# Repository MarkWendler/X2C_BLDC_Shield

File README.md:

# X2C_BLDC_Shield
BLDC motor driver expansion board for X2C+ development board

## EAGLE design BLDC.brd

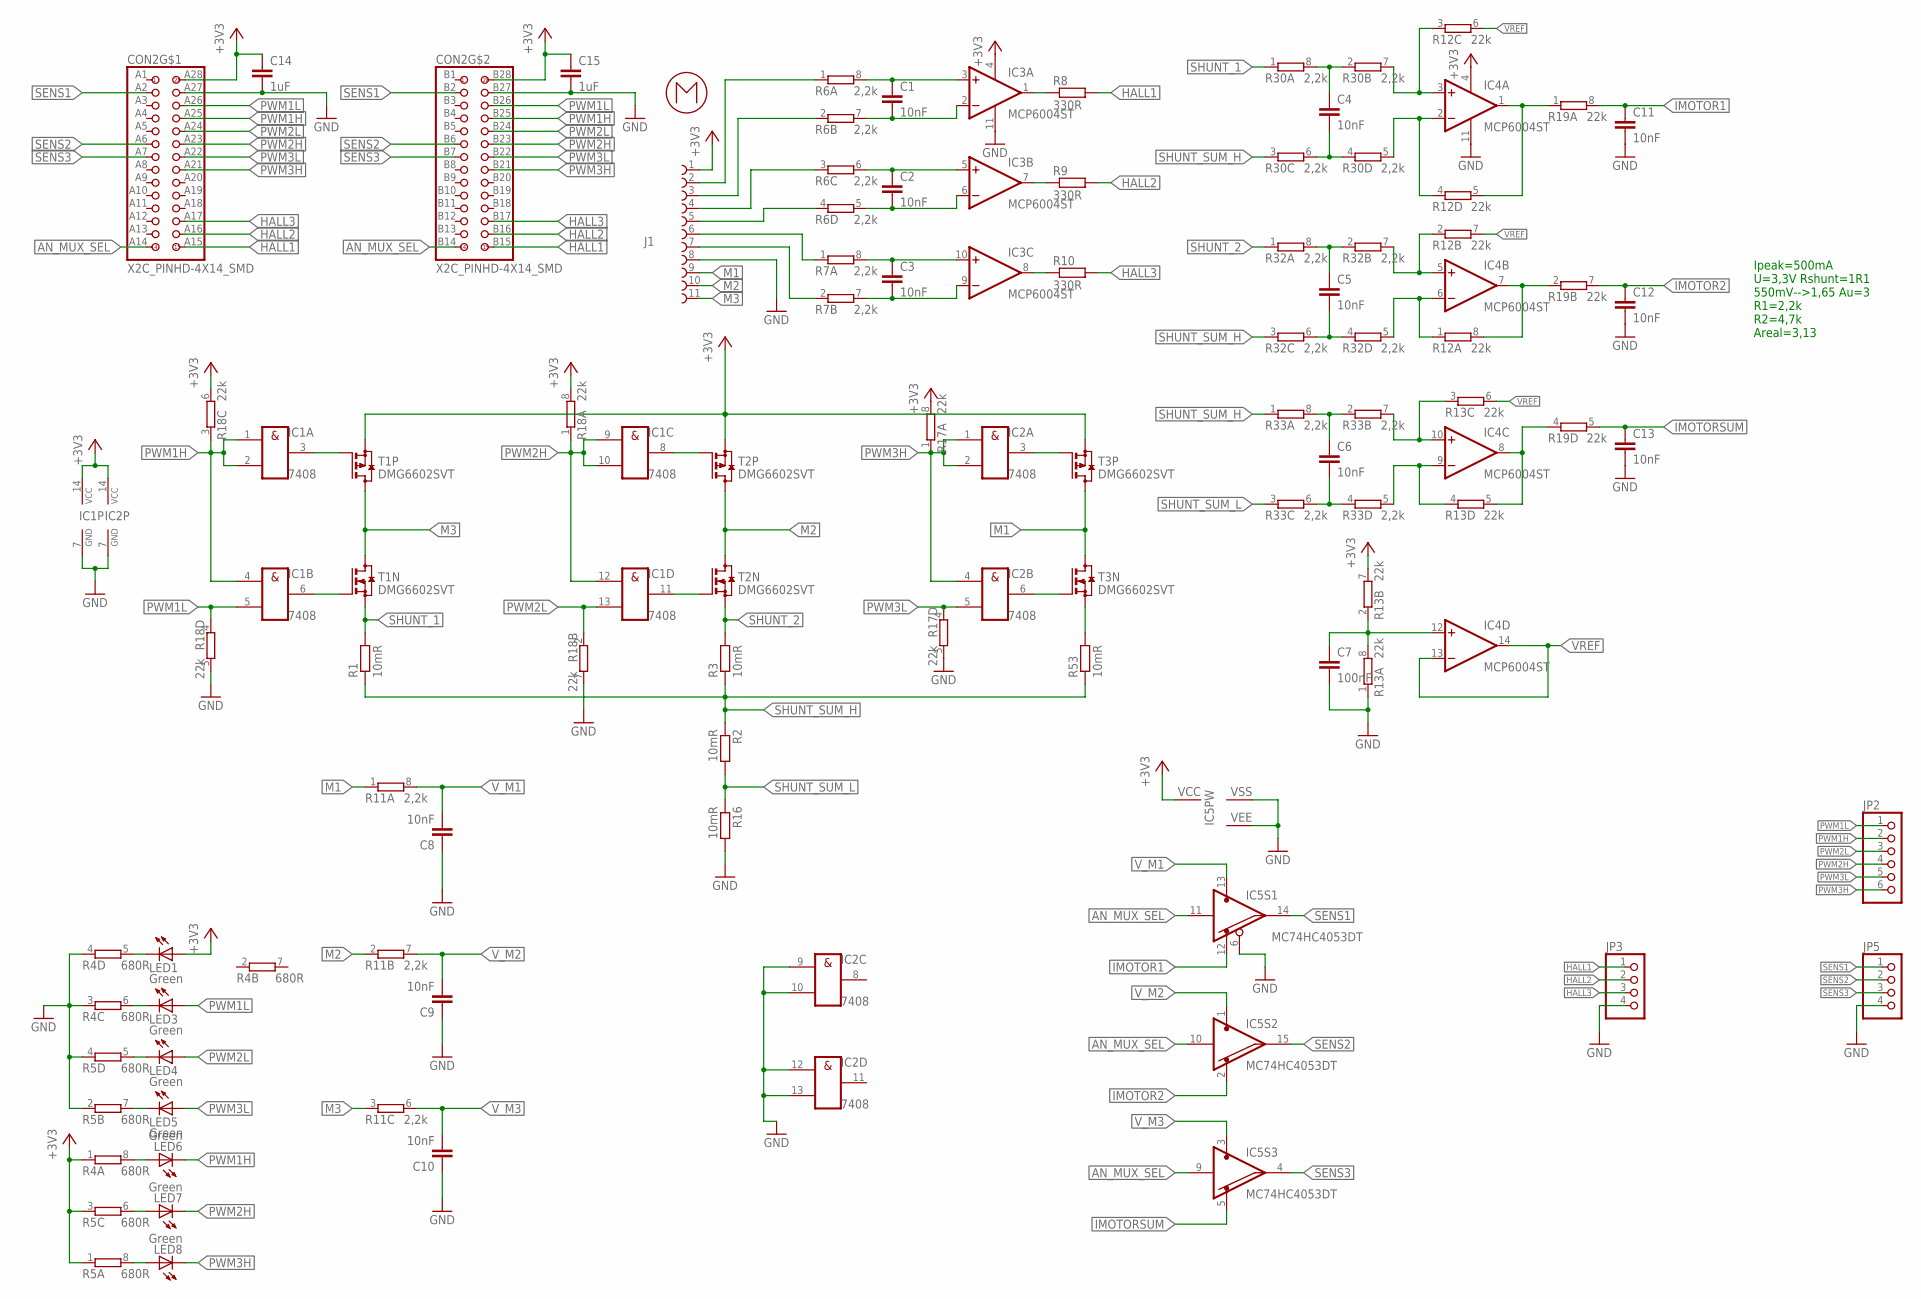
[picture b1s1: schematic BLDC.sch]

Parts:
C1, C2, C3, C4, C5, C6, C8, C9, C10, C11, C12, C13: 10nF; C0603K
C7: 100nF; C0603K
C14, C15: 1uF; C0603K
CON2: X2C_PINHD-4X14_SMD; X2C_4X14_SMD
IC1, IC2: 7408; TSSOP14
IC3, IC4: MCP6004ST; TSSOP14
IC5: MC74HC4053DT; TSSOP16
J1: 68611114122
JP2: PINHD-1X6; 1X06
JP3, JP5: PINHD-1X4; 1X04
LED1, LED3, LED4, LED5, LED6, LED7, LED8: Green; CHIPLED_0805
R1, R2, R3, R16, R53: 10mR; R1206
R4, R5: 680R; EXBV8V_A
R6, R7, R11, R30, R32, R33: 2,2k; EXBV8V_A
R8, R9, R10: 330R; R0603
R12, R13, R17, R18, R19: 22k; EXBV8V_A
T1, T2, T3: DMG6602SVT; TSOT23-6
U$2: BLDC_MOTOR

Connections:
+3V3: C14.1, C15.1, CON2.A28, CON2.B28 (A28), IC1.14 (VCC), IC2.14 (VCC), IC3.4 (V+), IC4.4 (V+), IC5.16 (VCC), J1.1, LED1.A, R4.1, R5.1, R5.3 (1), R13.7 (2), R17.8 (2), R18.6 (2), R18.8 (2), T1.2 (S), T2.2 (S), T3.2 (S)
AN_MUX_SEL: CON2.A14, CON2.B14 (A14), IC5.9 (I), IC5.10 (I), IC5.11 (I)
GND: C7.2, C8.1, C9.1, C10.1, C11.2, C12.2, C13.2, C14.2, C15.2, CON2.A27, CON2.B27 (A27), IC1.7 (GND), IC2.7 (GND), IC2.9 (I0), IC2.10 (I1), IC2.12 (I0), IC2.13 (I1), IC3.11 (V-), IC4.11 (V-), IC5.6, IC5.7 (VEE), IC5.8 (GND), J1.8, JP3.4, JP5.4, R4.3 (1), R4.4 (1), R5.2 (1), R5.4 (1), R13.1, R16.2, R17.5 (2), R18.5 (2), R18.7 (2)
HALL1: CON2.A15, CON2.B15 (A15), JP3.1, R8.2
HALL2: CON2.A16, CON2.B16 (A16), JP3.2, R9.2
HALL3: CON2.A17, CON2.B17 (A17), JP3.3, R10.2
IMOTOR1: C11.1, IC5.12 (O2), R19.8 (2)
IMOTOR2: C12.1, IC5.2 (O2), R19.7 (2)
IMOTORSUM: C13.1, IC5.5 (O2), R19.5 (2)
M1: J1.9, R11.1, T3.4 (D), T3.6 (D)
M2: J1.10, R11.2 (1), T2.4 (D), T2.6 (D)
M3: J1.11, R11.3 (1), T1.4 (D), T1.6 (D)
unnamed: IC1.3 (O), T1.3 (G)
unnamed: IC1.6 (O), T1.1 (G)
unnamed: IC1.8 (O), T2.3 (G)
unnamed: IC1.11 (O), T2.1 (G)
unnamed: IC2.3 (O), T3.3 (G)
unnamed: IC2.6 (O), T3.1 (G)
unnamed: C1.1, IC3.3 (+IN), R6.8 (2)
unnamed: C1.2, IC3.2 (-IN), R6.7 (2)
unnamed: IC4.8 (OUT), R13.5 (2), R19.4 (1)
unnamed: C5.1, R32.2 (1), R32.8 (2)
unnamed: C4.1, R30.2 (1), R30.8 (2)
unnamed: C4.2, R30.4 (1), R30.6 (2)
unnamed: IC4.3 (+IN), R12.3 (1), R30.7 (2)
unnamed: IC4.2 (-IN), R12.4 (1), R30.5 (2)
unnamed: C5.2, R32.4 (1), R32.6 (2)
unnamed: IC4.6 (-IN), R12.1, R32.5 (2)
unnamed: IC4.5 (+IN), R12.2 (1), R32.7 (2)
unnamed: C7.1, IC4.12 (+IN), R13.2 (1), R13.8 (2)
unnamed: IC3.8 (OUT), R10.1
unnamed: LED8.A, R5.8 (2)
unnamed: C6.1, R33.2 (1), R33.8 (2)
unnamed: IC4.10 (+IN), R13.3 (1), R33.7 (2)
unnamed: IC4.9 (-IN), R13.4 (1), R33.5 (2)
unnamed: C6.2, R33.4 (1), R33.6 (2)
unnamed: LED7.A, R5.6 (2)
unnamed: LED5.C, R5.7 (2)
unnamed: IC4.7 (OUT), R12.8 (2), R19.2 (1)
unnamed: C2.1, IC3.5 (+IN), R6.6 (2)
unnamed: LED4.C, R5.5 (2)
unnamed: LED6.A, R4.8 (2)
unnamed: LED3.C, R4.6 (2)
unnamed: LED1.C, R4.5 (2)
unnamed: IC4.1 (OUT), R12.5 (2), R19.1
unnamed: C2.2, IC3.6 (-IN), R6.5 (2)
unnamed: C3.2, IC3.9 (-IN), R7.7 (2)
unnamed: R53.2, T3.5 (S)
unnamed: C3.1, IC3.10 (+IN), R7.8 (2)
unnamed: J1.2, R6.1
unnamed: J1.3, R6.2 (1)
unnamed: J1.4, R6.3 (1)
unnamed: J1.5, R6.4 (1)
unnamed: J1.6, R7.1
unnamed: J1.7, R7.2 (1)
unnamed: IC3.1 (OUT), R8.1
unnamed: IC3.7 (OUT), R9.1
PWM1H: CON2.A25, CON2.B25 (A25), IC1.1 (I0), IC1.2 (I1), IC1.4 (I0), JP2.2, LED6.C, R18.3 (1)
PWM1L: CON2.A26, CON2.B26 (A26), IC1.5 (I1), JP2.1, LED3.A, R18.4 (1)
PWM2H: CON2.A23, CON2.B23 (A23), IC1.9 (I0), IC1.10 (I1), IC1.12 (I0), JP2.4, LED7.C, R18.1
PWM2L: CON2.A24, CON2.B24 (A24), IC1.13 (I1), JP2.3, LED4.A, R18.2 (1)
PWM3H: CON2.A21, CON2.B21 (A21), IC2.1 (I0), IC2.2 (I1), IC2.4 (I0), JP2.6, LED8.C, R17.1
PWM3L: CON2.A22, CON2.B22 (A22), IC2.5 (I1), JP2.5, LED5.A, R17.4 (1)
SENS1: CON2.A2, CON2.B2 (A2), IC5.14 (O), JP5.1
SENS2: CON2.A6, CON2.B6 (A6), IC5.15 (O), JP5.2
SENS3: CON2.A7, CON2.B7 (A7), IC5.4 (O), JP5.3
SHUNT_1: R1.2, R30.1, T1.5 (S)
SHUNT_2: R3.2, R32.1, T2.5 (S)
SHUNT_SUM_H: R1.1, R2.1, R3.1, R30.3 (1), R32.3 (1), R33.1, R53.1
SHUNT_SUM_L: R2.2, R16.1, R33.3 (1)
VREF: IC4.13 (-IN), IC4.14 (OUT), R12.6 (2), R12.7 (2), R13.6 (2)
V_M1: C8.2, IC5.13 (O1), R11.8 (2)
V_M2: C9.2, IC5.1 (O1), R11.7 (2)
V_M3: C10.2, IC5.3 (O1), R11.6 (2)

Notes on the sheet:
Ipeak=500mA U=3,3V Rshunt=1R1 550mV-->1,65 Au=3 R1=2,2k R2=4,7k Areal=3,13

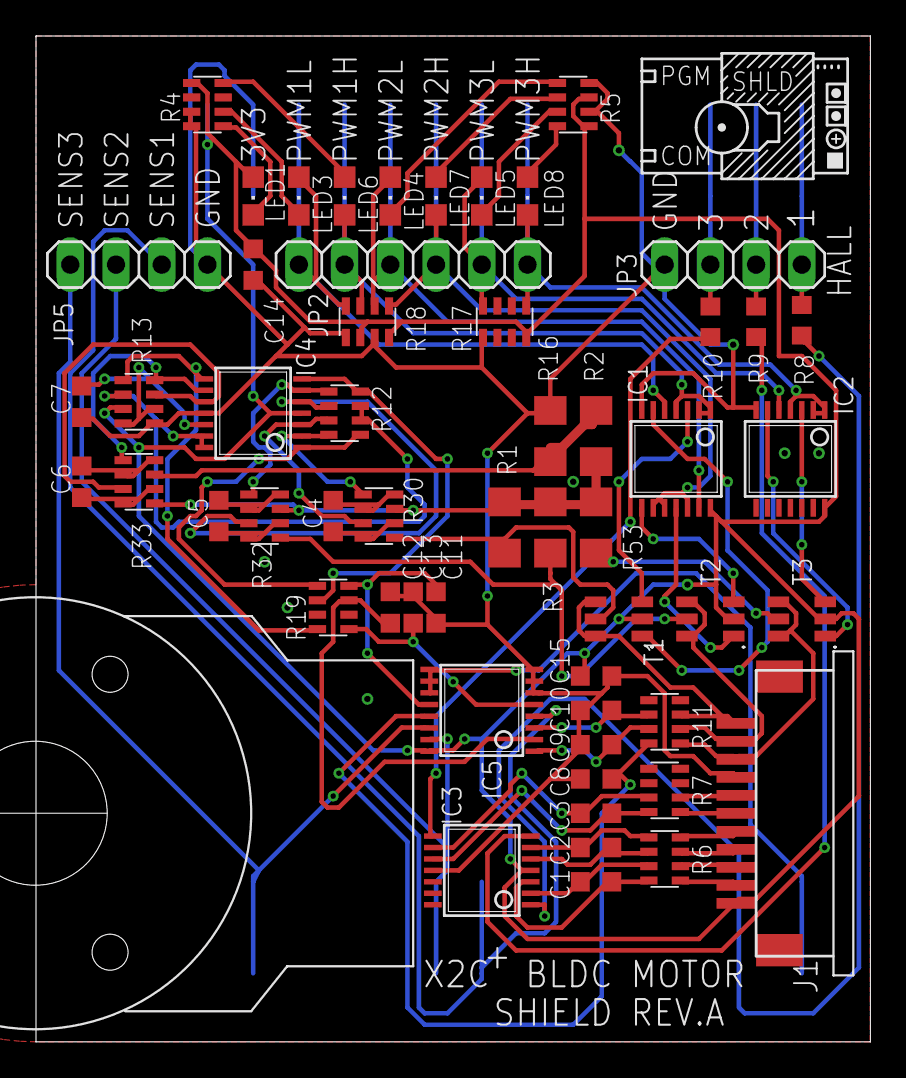
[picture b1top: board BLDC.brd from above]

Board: 2 copper layers, 46.4 x 55.9 mm, 57 parts (1 on the bottom side), 74 nets.

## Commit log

2018-08-02 BLDC REVA
2018-08-02 Added MPLAB X ignore list
    Now the MPLAB X project can be pushed to github
2018-08-02 BLDC spinning project dsPIC
    Full speed BLDC spinning
2020-02-19 Project updated to MPLAB X 5.30 + updated gitignore
2020-02-20 Updated peripheral drivers for newest MCC. Also updated commutation logic.
2020-02-21 Commutation sequence fixed, high side driving inverted (PNP)
2020-02-21 PWM freq increased, ADC scaling and duty cycle is changed to reach max BLDC performance
2020-02-21 ADC interrupt added for POT measurement and duty cycle update
2025-11-14 Add schematics pdf format
2025-11-14 Increased PWM freq and added Timer2 for speed
2025-11-14 Fixing project config

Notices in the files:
parts and their libraries:
Wurth_Elektronik_Electromechanic_FPC_Con: Copyright: Würth Elektronik
